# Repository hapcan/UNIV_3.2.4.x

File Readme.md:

UNIV 3.2.4.x
============

RELAY MODULE - 6 bistable 16A relays for DIN rail

Device webpage: http://hapcan.com/devices/universal/univ_3/univ_3-2-4-x/

Hardware created in Eagle PCB Software http://www.cadsoftusa.com/

Firmware created in Microchip MPLAB http://www.microchip.com/mplabide/ in assembly language

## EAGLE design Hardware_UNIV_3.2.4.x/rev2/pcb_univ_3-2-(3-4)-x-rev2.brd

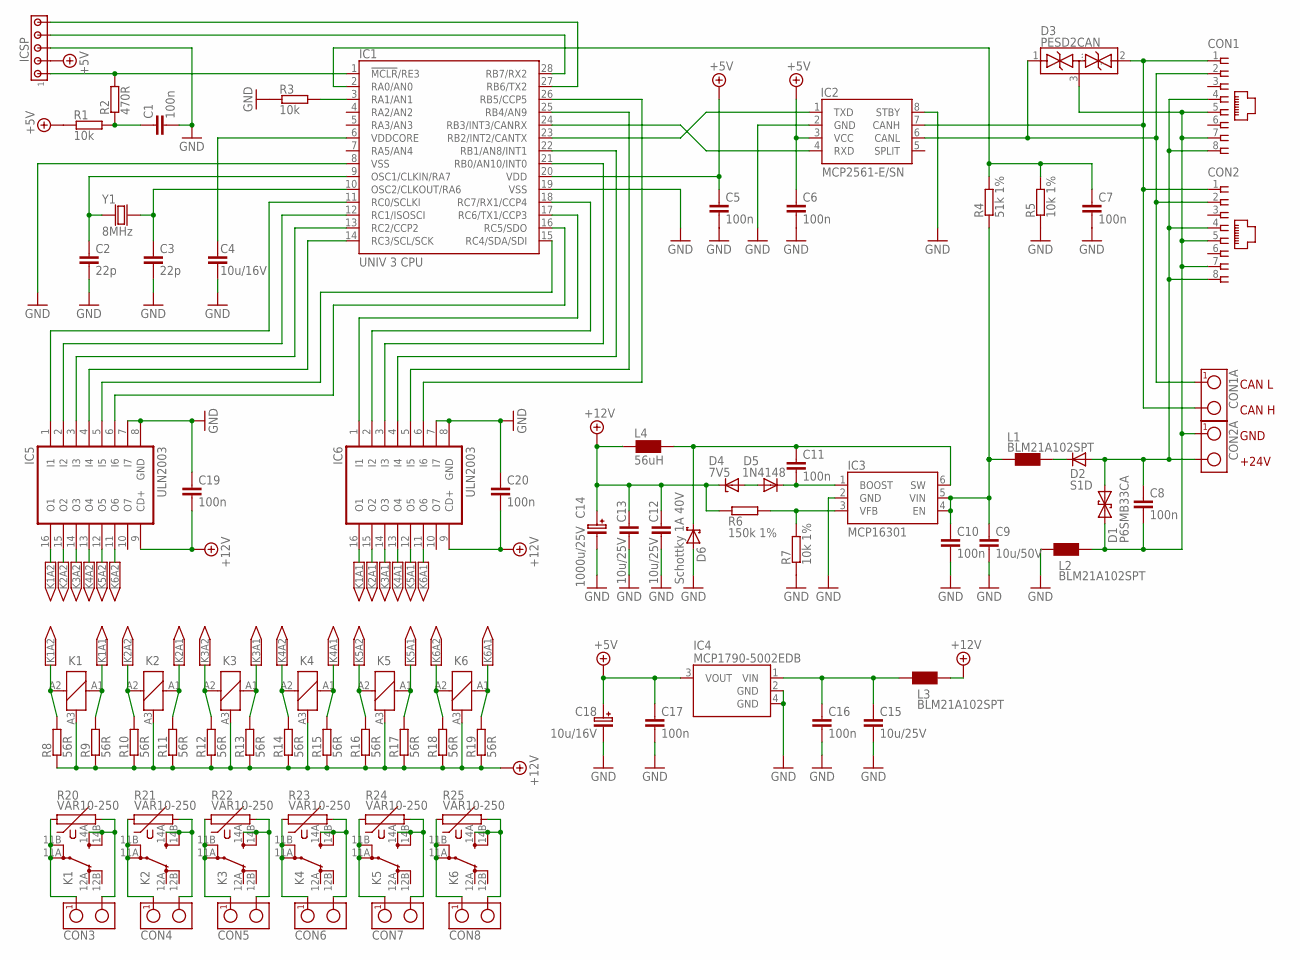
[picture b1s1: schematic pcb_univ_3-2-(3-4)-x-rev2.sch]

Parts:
C1, C5, C6, C7, C8, C10, C11, C16, C17, C19, C20: 100n; 0805
C2, C3: 22p; 0805
C4: 10u/16V; 0805
C9: 10u/50V; 1210
C12, C13, C15: 10u/25V; 1206
C14: 1000u/25V; CAP-5X10.5
C18: 10u/16V; SMC_B
CON1, CON2: RJ45-SOCKET; RJ45-PCB-SOCKET
CON1A, CON2A: TERMINAL-2; ARK2-5X10,5MM
CON3, CON4, CON5, CON6, CON7, CON8: TERMINAL-2; ARK2-7.5X10.5MM
D1: P6SMB33CA; DO-214_TRANSIL2
D2: S1D; DO-214
D3: PESD2CAN; SOT-23
D4: 7V5; SOD-80
D5: 1N4148; 0805
D6: Schottky 1A 40V; DO-214
IC1: UNIV 3 CPU; UNIV3CPU
IC2: MCP2561-E/SN; SO-08
IC3: MCP16301; SOT-23-6
IC4: MCP1790-5002EDB; SOT-223
IC5, IC6: ULN2003; SO-16
ICSP: HEADER5; SIP-5
K1, K2, K3, K4, K5, K6: RELAY_RT
L1, L2, L3: BLM21A102SPT; 0805
L4: 56uH; CHOKE-DER0705
R1, R3: 10k; 0805
R2: 470R; 0805
R4: 51k 1%; 0805
R5, R7: 10k 1%; 0805
R6: 150k 1%; 0805
R8, R9, R10, R11, R12, R13, R14, R15, R16, R17, R18, R19: 56R; 1206
R20, R21, R22, R23, R24, R25: VAR10-250; VARISTOR1
Y1: 8MHz; CRYSTAL-HC49V

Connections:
+5V: C5.1, C6.1, C17.1, C18.+ (1), IC1.20 (VDD), IC2.3 (VCC), IC4.3 (VOUT), ICSP.2, R1.1
+12V: C12.1, C13.1, C14.+ (1), C19.2, C20.2, D4.C, IC5.9 (CD+), IC6.9 (CD+), K1.A3 (-), K2.A3 (-), K3.A3 (-), K4.A3 (-), K5.A3 (-), K6.A3 (-), L3.2, L4.1, R6.1, R8.1, R9.1, R10.1, R11.1, R12.1, R13.1, R14.1, R15.1, R16.1, R17.1, R18.1, R19.1
GND: C1.2, C2.2, C3.2, C4.2, C5.2, C6.2, C7.2, C9.2, C10.2, C12.2, C13.2, C14.- (2), C15.2, C16.2, C17.2, C18.- (2), C19.1, C20.1, D6.A, IC1.8 (VSS), IC1.19 (VSS), IC2.2 (GND), IC2.8 (STBY), IC3.2 (GND), IC4.2 (GND), IC4.4 (GND), IC5.7 (I7), IC5.8 (GND), IC6.7 (I7), IC6.8 (GND), ICSP.3, L2.1, R3.1, R5.1, R7.1
K1A1: IC6.16 (O1), K1.A1 (S+), R9.2
K1A2: IC5.16 (O1), K1.A2 (R+), R8.2
K2A1: IC6.15 (O2), K2.A1 (S+), R11.2
K2A2: IC5.15 (O2), K2.A2 (R+), R10.2
K3A1: IC6.14 (O3), K3.A1 (S+), R13.2
K3A2: IC5.14 (O3), K3.A2 (R+), R12.2
K4A1: IC6.13 (O4), K4.A1 (S+), R15.2
K4A2: IC5.13 (O4), K4.A2 (R+), R14.2
K5A1: IC6.12 (O5), K5.A1 (S+), R17.2
K5A2: IC5.12 (O5), K5.A2 (R+), R16.2
K6A1: IC6.11 (O6), K6.A1 (S+), R19.2
K6A2: IC5.11 (O6), K6.A2 (R+), R18.2
unnamed: D2.C, L1.2
unnamed: IC1.24 (RB3/INT3/CANRX), IC2.4 (RXD)
unnamed: IC1.23 (RB2/INT2/CANTX), IC2.1 (TXD)
unnamed: CON1.1, CON1A.2, CON2.1, D3.2 (..), IC2.7 (CANH)
unnamed: C9.1, C10.1, IC3.4 (EN), IC3.5 (VIN), L1.1, R4.1
unnamed: C15.1, C16.1, IC4.1 (VIN), L3.1
unnamed: C1.1, R1.2, R2.1
unnamed: IC1.1 (!MCLR!/RE3), ICSP.1, R2.2
unnamed: C8.1, CON1.4, CON1.8, CON2.4, CON2.8, CON2A.2, D1.C (2), D2.A
unnamed: IC1.28 (RB7/RX2), ICSP.4
unnamed: IC1.12 (RC1/ISOSCI), IC5.2 (I2)
unnamed: IC1.3 (RA1/AN1), R3.2
unnamed: C8.2, CON1.5, CON1.7, CON2.5, CON2.7, CON2A.1, D1.A (1), D3.3 (...), L2.2
unnamed: IC1.27 (RB6/TX2), ICSP.5
unnamed: C3.1, IC1.10 (OSC2/CLKOUT/RA6), Y1.2
unnamed: C7.1, IC1.2 (RA0/AN0), R4.2, R5.2
unnamed: C11.1, D6.C, IC3.6 (SW), L4.2
unnamed: IC1.11 (RC0/SCLKI), IC5.1 (I1)
unnamed: IC1.13 (RC2/CCP2), IC5.3 (I3)
unnamed: IC3.3 (VFB), R6.2, R7.2
unnamed: IC1.14 (RC3/SCL/SCK), IC5.4 (I4)
unnamed: D4.A, D5.2 (A)
unnamed: IC1.15 (RC4/SDA/SDI), IC5.5 (I5)
unnamed: CON1.2, CON1A.1, CON2.2, D3.1 (.), IC2.6 (CANL)
unnamed: CON3.1, K1.11A (PA), K1.11B (PB), R20.1
unnamed: CON3.2, K1.14A (SA), K1.14B (SB), R20.2
unnamed: C11.2, D5.1 (C), IC3.1 (BOOST)
unnamed: C2.1, IC1.9 (OSC1/CLKIN/RA7), Y1.1
unnamed: IC1.16 (RC5/SDO), IC5.6 (I6)
unnamed: IC1.17 (RC6/TX1/CCP3), IC6.1 (I1)
unnamed: IC1.18 (RC7/RX1/CCP4), IC6.2 (I2)
unnamed: CON4.2, K2.14A (SA), K2.14B (SB), R21.2
unnamed: CON5.2, K3.14A (SA), K3.14B (SB), R22.2
unnamed: CON6.2, K4.14A (SA), K4.14B (SB), R23.2
unnamed: CON7.2, K5.14A (SA), K5.14B (SB), R24.2
unnamed: CON8.2, K6.14A (SA), K6.14B (SB), R25.2
unnamed: C4.1, IC1.6 (VDDCORE)
unnamed: CON4.1, K2.11A (PA), K2.11B (PB), R21.1
unnamed: CON5.1, K3.11A (PA), K3.11B (PB), R22.1
unnamed: CON6.1, K4.11A (PA), K4.11B (PB), R23.1
unnamed: CON7.1, K5.11A (PA), K5.11B (PB), R24.1
unnamed: CON8.1, K6.11A (PA), K6.11B (PB), R25.1
unnamed: IC1.21 (RB0/AN10/INT0), IC6.3 (I3)
unnamed: IC1.22 (RB1/AN8/INT1), IC6.4 (I4)
unnamed: IC1.25 (RB4/AN9), IC6.5 (I5)
unnamed: IC1.26 (RB5/CCP5), IC6.6 (I6)

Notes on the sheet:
CAN L
CAN H
GND
+24V

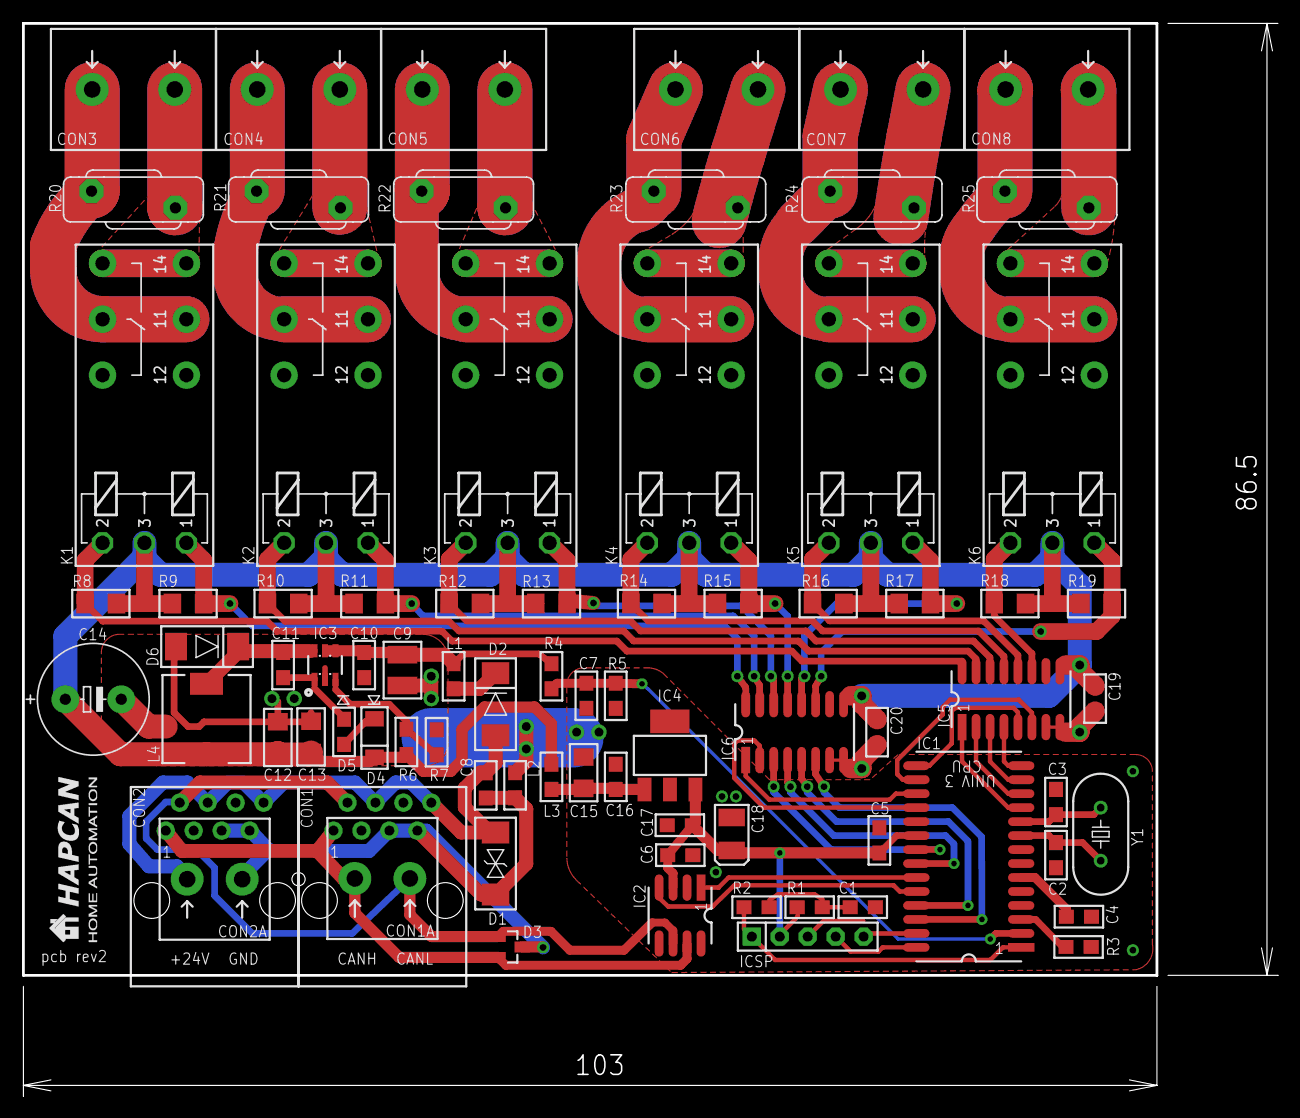
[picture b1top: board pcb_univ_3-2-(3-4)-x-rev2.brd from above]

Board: 2 copper layers, 113.9 x 97.4 mm, 79 parts (0 on the bottom side), 61 nets.

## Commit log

2013-09-25 hardware revision 1
2013-09-25 firmware revision 0
2015-03-16 firmware UNIV 3.2.4.0 rev0
2015-03-16 firmware UNIV_3.2.4.1 rev0
2015-03-16 firmware UNIV 3.2.4.1 rev0
2015-04-01 hardware UNIV 3.2.4.x rev1
2015-04-01 hardware UNIV 3.2.4.x rev2
2015-09-26 firmware UNIV 3.2.4.1 rev1
2018-03-04 firmware UNIV 3.2.4.2 revision 0
2022-10-07 firmware UNIV 3.2.4.3 revision 0
